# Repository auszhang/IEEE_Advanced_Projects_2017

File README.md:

# IEEE_Advanced_Projects_2017
Project by Austin Zhang, Ashwin Narkar, Kenny Chan, Christine Chen. 9/2017 - Present

See repository ashwin-narkar/AdvancedProjects-2017 for group contributions.

This repository is for my own reference.

Private files (not included...yet)
- Bill of Materials
- Design review slides

2/15/17

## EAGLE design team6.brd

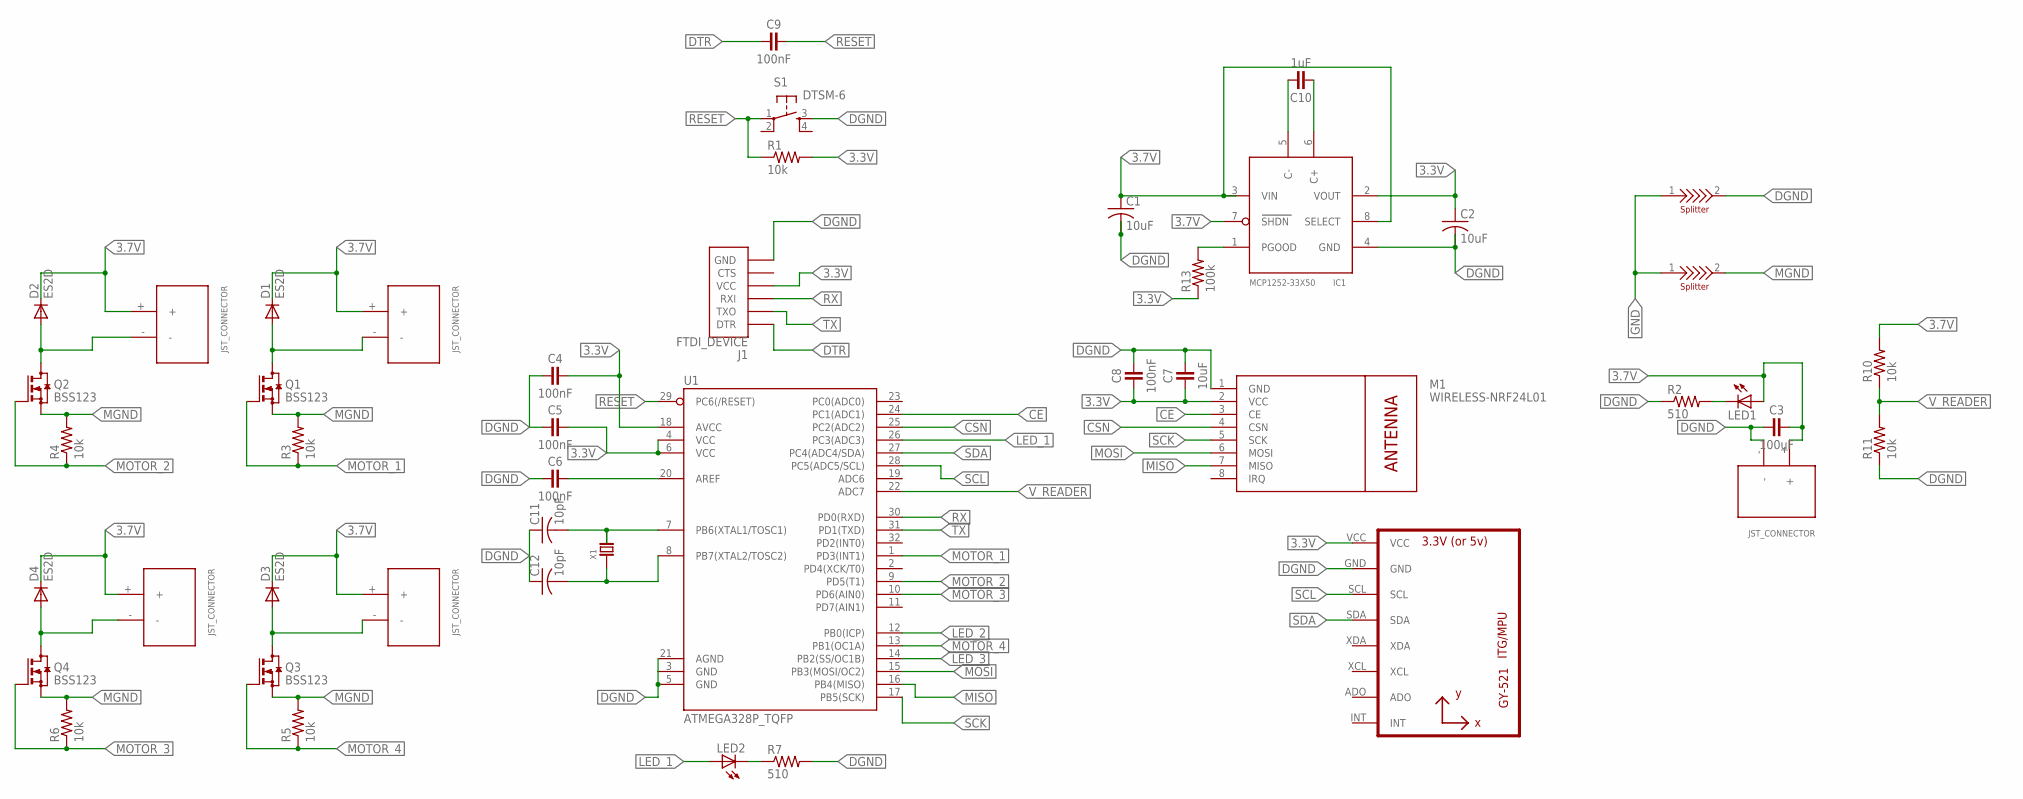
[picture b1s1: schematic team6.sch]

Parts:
C1, C2: 10uF; C1206
C3: 100uF; C1206
C4, C5, C6, C8, C9: 100nF; C0603
C7: 10uF; C0603
C10: 1uF; C0603
C11, C12: 10pF; RCL_C0603K
D1, D2, D3, D4: ES2D; SMB
IC1: MCP1252-33X50; MSOP8
J1: FTDI_DEVICE; FTDI_DEVICE_SIDE
JST_MOTOR_1: JST_MOTOR_1; JST_CONNECTOR_FEMALE
LED1, LED2: LED_ESML0603; LED_SML0603
M1: WIRELESS-NRF24L01
Q1, Q2, Q3, Q4: BSS123; SOT23
R1, R3, R4, R5, R6, R10, R11: 10k; 0603
R2, R7: 510; 0603
R13: 100k; 0603
S1: DTSM-6
U1: ATMEGA328P_TQFP; TQFP32-08
U3: GY-521MPU6050; GY-521
U$2, U$3, U$4, U$5: JST_CONNECTOR_FEMALE
U$7, U$8: SPLITTER
X1: CRYSTAL-NX3225GD; NDK-NX3225GD

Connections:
3.3V: C2.1, C4.2, C5.2, C7.1, C8.1, IC1.2 (VOUT), J1.P$4 (VCC), M1.2 (VCC), R1.2, R13.1, U1.4 (VCC), U1.6 (VCC), U1.18 (AVCC), U3.VCC
3.7V: C1.1, C3.2, D1.C, D2.C, D3.C, D4.C, IC1.3 (VIN), IC1.7 (SHDN), IC1.8 (SELECT), JST_MOTOR_1.+, LED1.A, R10.2, U$2.+, U$3.+, U$4.+, U$5.+
CE: M1.3 (CE), U1.24 (PC1(ADC1))
CSN: M1.4 (CSN), U1.25 (PC2(ADC2))
DGND: C1.2, C2.2, C3.1, C4.1, C5.1, C6.1, C7.2, C8.2, C11.1, C12.1, IC1.4 (GND), J1.P$6 (GND), M1.1 (GND), R2.1, R7.2, R11.1, S1.3, U1.3 (GND), U1.5 (GND), U1.21 (AGND), U3.GND, U$2.-, U$8.2
DTR: C9.1, J1.P$1 (DTR)
GND: U$7.1, U$8.1
LED_1: LED2.A, U1.26 (PC3(ADC3))
LED_2: U1.12 (PB0(ICP))
LED_3: U1.14 (PB2(SS/OC1B))
MGND: Q1.2 (S), Q2.2 (S), Q3.2 (S), Q4.2 (S), R3.2, R4.2, R5.2, R6.2, U$7.2
MISO: M1.7 (MISO), U1.16 (PB4(MISO))
MOSI: M1.6 (MOSI), U1.15 (PB3(MOSI/OC2))
MOTOR_1: Q1.1 (G), R3.1, U1.1 (PD3(INT1))
MOTOR_2: Q2.1 (G), R4.1, U1.9 (PD5(T1))
MOTOR_3: Q4.1 (G), R6.1, U1.10 (PD6(AIN0))
MOTOR_4: Q3.1 (G), R5.1, U1.13 (PB1(OC1A))
unnamed: D2.A, Q2.3 (D), U$3.-
unnamed: D1.A, JST_MOTOR_1.-, Q1.3 (D)
unnamed: D3.A, Q3.3 (D), U$5.-
unnamed: D4.A, Q4.3 (D), U$4.-
unnamed: LED1.C, R2.2
unnamed: C11.2, U1.7 (PB6(XTAL1/TOSC1)), X1.2
unnamed: C12.2, U1.8 (PB7(XTAL2/TOSC2)), X1.1
unnamed: C6.2, U1.20 (AREF)
unnamed: C10.2, IC1.5 (C-)
unnamed: C10.1, IC1.6 (C+)
unnamed: LED2.C, R7.1
PGOOD: IC1.1 (PGOOD), R13.2
RESET: C9.2, R1.1, S1.1, U1.29 (PC6(/RESET))
RX: J1.P$3 (RXI), U1.30 (PD0(RXD))
SCK: M1.5 (SCK), U1.17 (PB5(SCK))
SCL: U1.28 (PC5(ADC5/SCL)), U3.SCL
SDA: U1.27 (PC4(ADC4/SDA)), U3.SDA
TX: J1.P$2 (TXO), U1.31 (PD1(TXD))
V_READER: R10.1, R11.2, U1.22 (ADC7)

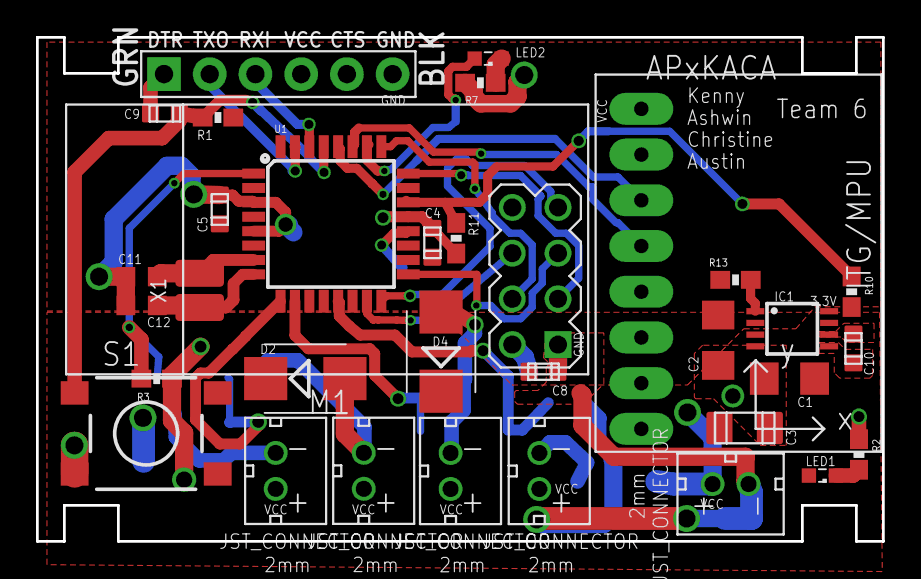
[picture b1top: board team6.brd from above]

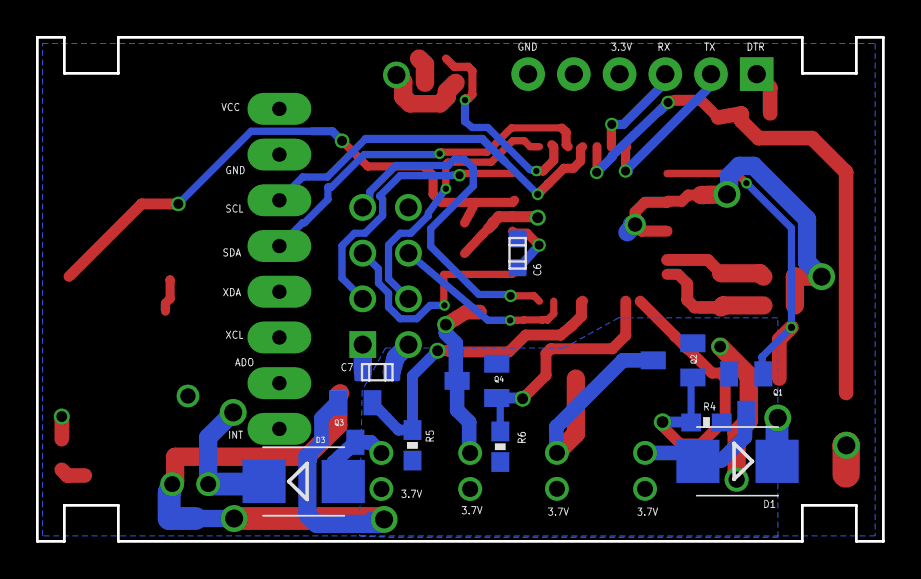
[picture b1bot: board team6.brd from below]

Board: 2 copper layers, 47.0 x 28.0 mm, 46 parts (13 on the bottom side), 34 nets.

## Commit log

2018-02-15 Initial commit
    Added all files
2018-02-21 Removed unnecessary files, added final board and schemaatic
    Final PCB and SCH: team6.brd, team6.sch

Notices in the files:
parts and their libraries:
SparkFun-Resistors: Licensing: Creative Commons ShareAlike 4.0 International - https://creativecommons.org/licenses/by-sa/4.0
